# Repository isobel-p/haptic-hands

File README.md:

# haptic-hands
> A PCB fidget toy with haptic feedback for ultimate satisfaction. Good to help you relax, or somewhere to put your hands in an awkward social encounter.

Want a better viewing experience? [Read it here instead.](https://isobel-p.loves-being-a.dev/haptic-hands)

*(note to Journey voters: I forgot to upload my last update - oops... I finally arranged all the components and routed the PCB. I didn't get time to add silkscreen designs but I'm finally happy with how it turned out.)*

## Features
- Powered by one CR2032 battery. They're pretty cheap and most people should have some.
- 7x4cm (roughly) for a compact theraputic experience, fits in most pockets.
- The golden trio of satisfying sensations: pretty flashing lights, gentle vibration and the most satisfying buttons your fingers have ever touched.
- Designed for human hands so you won't get hand cramp from using it. You're welcome.
- Made with basic components so it won't break the bank.

## Components
|Component|Quantity|
|---------|--------|
|CR2032 Battery Cell|x1|
|6mm Push Button|x8|
|5mm LED|x6|
|Resistor|x6|
|Capacitor|x1|
|Potentiometer|x1|
|Mini Motor Disk|x1|

*The final schematic. My first attempt only had one button, but what fun would that be?!*

## Solder - 3D View
Download the STEP file in this repo or [check it out here.](https://autode.sk/4cU02na)

*Living in Flatland? Here's a screenshot.*

## The Journey
Ok kids, story time...

This was my first real PCB and wow was it hard. Looking at a blank KiCad schematic for the first time was scary. I kinda forgot to post updates somewhere in the middle, and I completely forgot to commit my changes so I just uploaded everything in massive chunks. I spent so many hours doing this that I really needed to spend revising for tests for the new school term.

But it was worth it.

Looking back after these ten days, I have something tangible, that I'll hopefully be able to hold in my human hands and use in my everyday life. This is something that I really needed, to keep me occupied in the quiet moments in everyday life, and I hope it's something you'll need too. Thank you to the people watching my journey, especially the nine of you who followed me in the end. It really helped, believe me. Thank you <3

## Contact Information
I'm @isobel-p on GitHub, HC Slack and most other socials.

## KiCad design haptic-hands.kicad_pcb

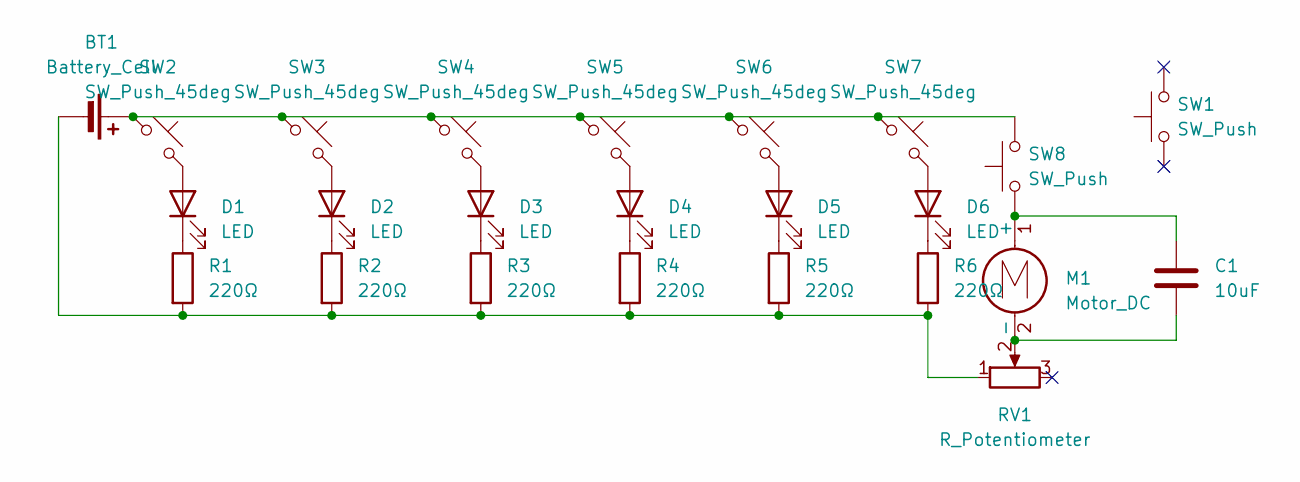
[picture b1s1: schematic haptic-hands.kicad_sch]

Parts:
BT1: Battery_Cell; BatteryHolder_Keystone_3034_1x20mm
C1: 10uF; CP_Radial_D8.0mm_P5.00mm
D1, D2, D3, D4, D5, D6: LED; LED_D5.0mm
M1: Motor_DC; PinHeader_1x02_P2.54mm_Vertical
R1, R2, R3, R4, R5, R6: 220Ω; R_Axial_DIN0207_L6.3mm_D2.5mm_P7.62mm_Horizontal
RV1: R_Potentiometer; Potentiometer_Vishay_T73YP_Vertical
SW1, SW8: SW_Push; SW_PUSH_6mm
SW2, SW3, SW4, SW5, SW6, SW7: SW_Push_45deg; SW_PUSH_6mm

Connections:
unnamed: BT1.1 (+), SW2.1, SW3.1, SW4.1, SW5.1, SW6.1, SW7.1, SW8.2
unnamed: BT1.2 (-), R1.2, R2.2, R3.2, R4.2, R5.2, R6.2, RV1.1
unnamed: D1.2 (A), SW2.2
unnamed: D1.1 (K), R1.1
unnamed: D2.2 (A), SW3.2
unnamed: D2.1 (K), R2.1
unnamed: D3.2 (A), SW4.2
unnamed: D3.1 (K), R3.1
unnamed: D4.2 (A), SW5.2
unnamed: D4.1 (K), R4.1
unnamed: D5.2 (A), SW6.2
unnamed: D5.1 (K), R5.1
unnamed: D6.2 (A), SW7.2
unnamed: D6.1 (K), R6.1
unnamed: C1.1, M1.1 (+), SW8.1
unnamed: C1.2, M1.2 (-), RV1.2

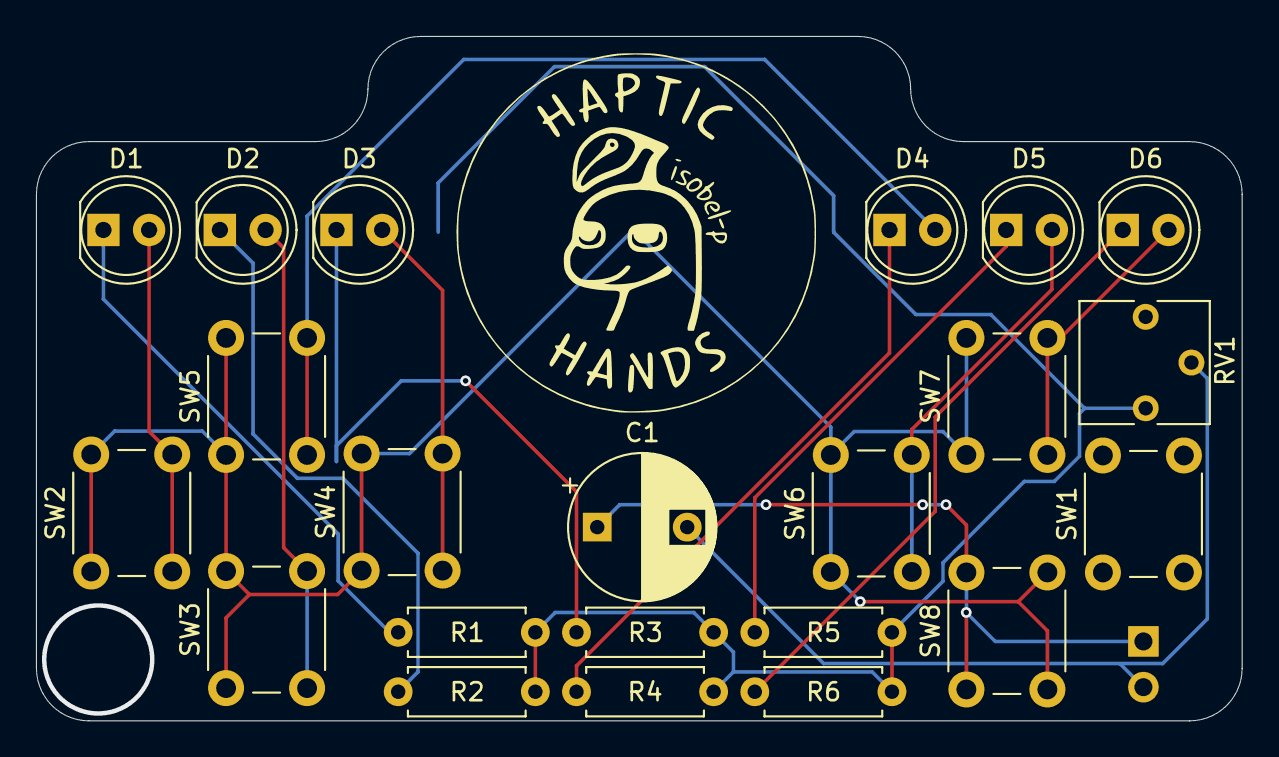
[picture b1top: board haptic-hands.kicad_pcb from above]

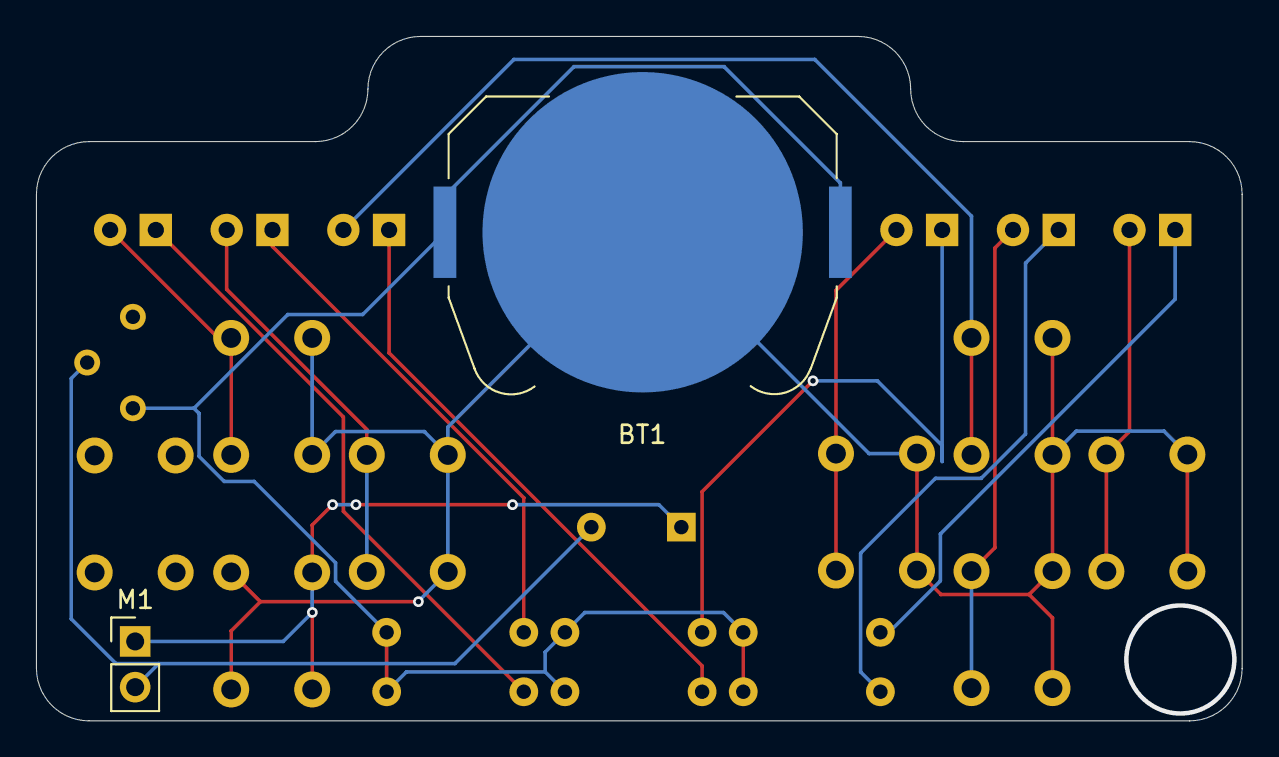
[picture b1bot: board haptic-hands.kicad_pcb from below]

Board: 2 copper layers, 67.0 x 38.0 mm, 24 parts (2 on the bottom side), 16 nets.

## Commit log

2025-04-14 Upload blank schematic and pcb
2025-04-17 Finish schematic
    larger commit, forgot to commit earlier
2025-04-18 Add LEDs
2025-04-18 Place components on pcb
2025-04-19 Rearrange components, create board outline, route
2025-04-22 Route PCB
2025-04-22 Rework schematic
2025-04-24 Rework PCB
2025-04-27 Change layout (again)
2025-04-27 Export final STEP file
2025-04-27 Create README, documentation link, gerbers and drill files
2025-05-15 Change schematic & pcb layout again
2025-05-15 Add Haptic Hands logo
